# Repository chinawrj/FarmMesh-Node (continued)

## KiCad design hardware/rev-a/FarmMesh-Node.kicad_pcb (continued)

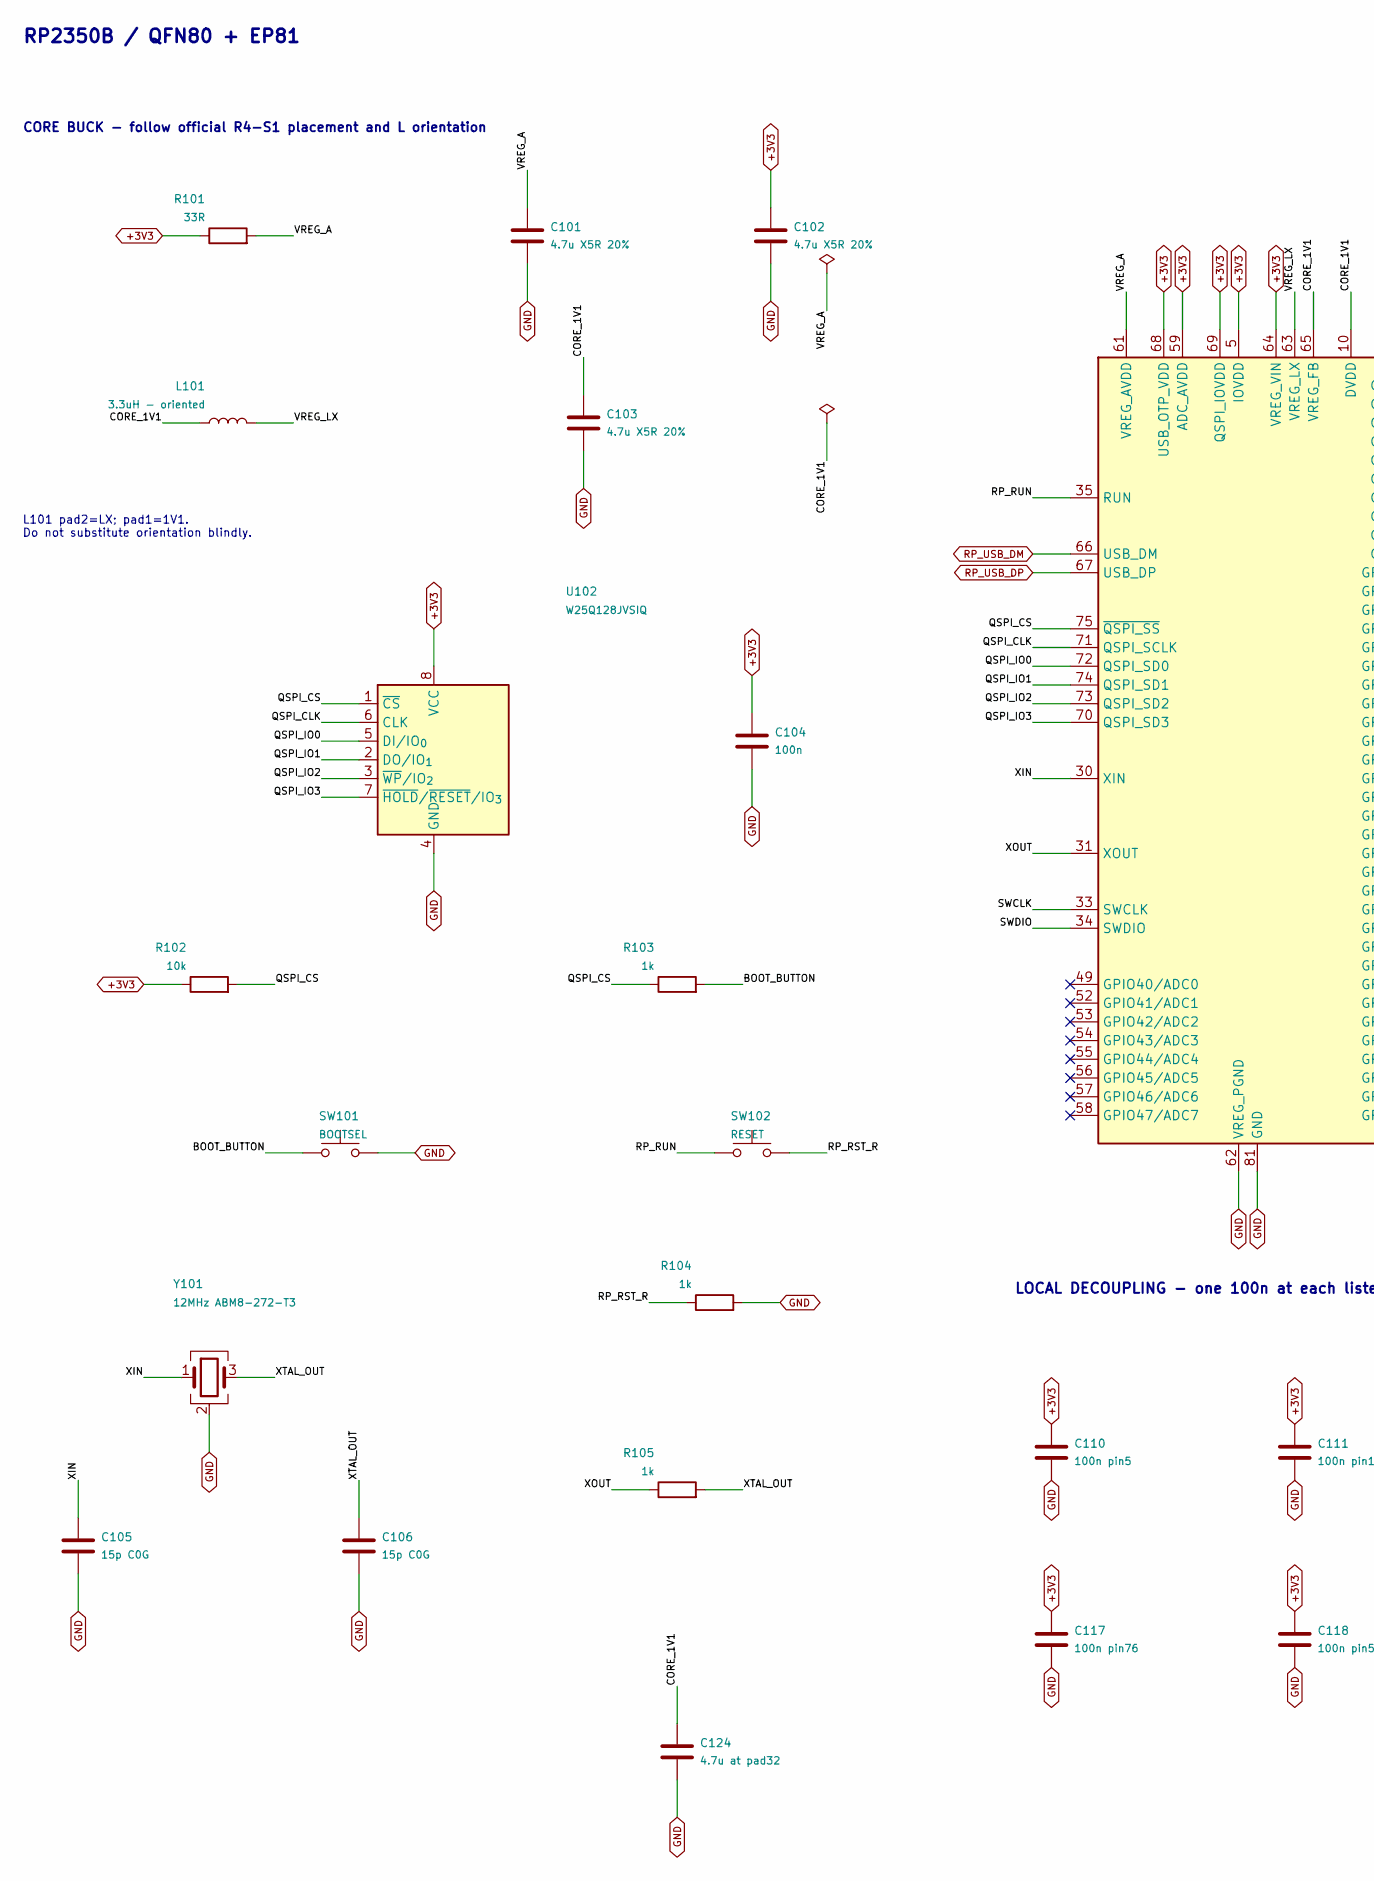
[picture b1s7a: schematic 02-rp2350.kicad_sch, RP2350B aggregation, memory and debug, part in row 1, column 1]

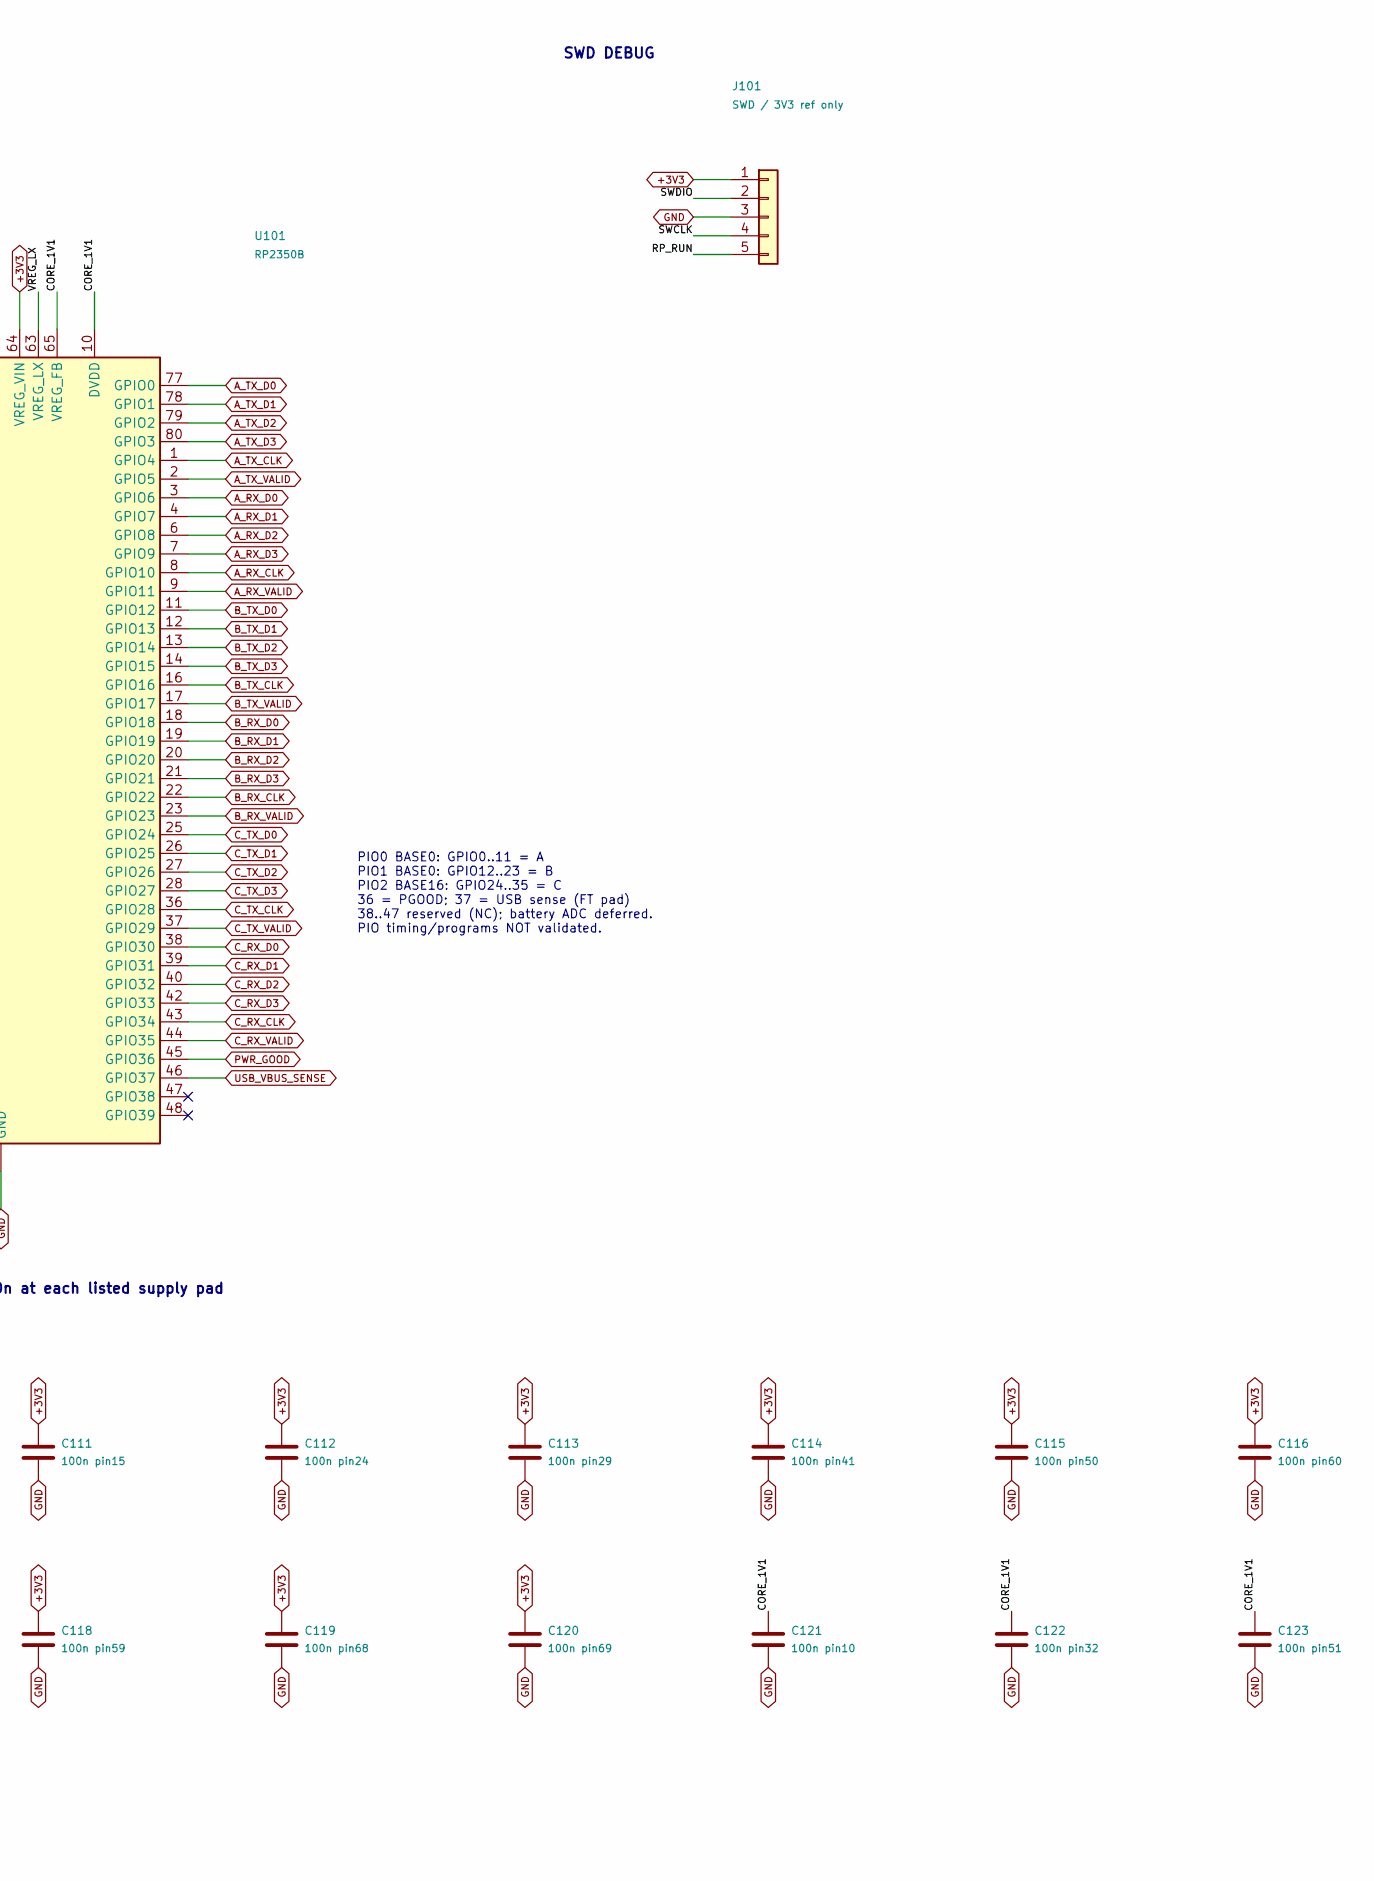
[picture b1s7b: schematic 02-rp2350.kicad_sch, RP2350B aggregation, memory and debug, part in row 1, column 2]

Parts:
C101, C102, C103: 4.7u X5R 20%; C_0603_1608Metric
C104: 100n; C_0603_1608Metric
C105, C106: 15p C0G; C_0603_1608Metric
C110: 100n pin5; C_0603_1608Metric
C111: 100n pin15; C_0603_1608Metric
C112: 100n pin24; C_0603_1608Metric
C113: 100n pin29; C_0603_1608Metric
C114: 100n pin41; C_0603_1608Metric
C115: 100n pin50; C_0603_1608Metric
C116: 100n pin60; C_0603_1608Metric
C117: 100n pin76; C_0603_1608Metric
C118: 100n pin59; C_0603_1608Metric
C119: 100n pin68; C_0603_1608Metric
C120: 100n pin69; C_0603_1608Metric
C121: 100n pin10; C_0603_1608Metric
C122: 100n pin32; C_0603_1608Metric
C123: 100n pin51; C_0603_1608Metric
C124: 4.7u at pad32; C_0603_1608Metric
J101: SWD / 3V3 ref only; PinHeader_1x05_P2.54mm_Vertical
L101: 3.3uH - oriented; AOTA-B201610S3R3-101-T; MPN AOTA-B201610S3R3-101-T
R101: 33R; R_0603_1608Metric
R102: 10k; R_0603_1608Metric
R103, R104, R105: 1k; R_0603_1608Metric
SW101: BOOTSEL; SW_Push_1P1T_NO_E-Switch_TL3301NxxxxxG
SW102: RESET; SW_Push_1P1T_NO_E-Switch_TL3301NxxxxxG
U101: RP2350B; QFN-80-1EP_10x10mm_P0.4mm_EP3.4x3.4mm; MPN RP2350B
U102: W25Q128JVSIQ; SOIC-8_5.3x5.3mm_P1.27mm; MPN W25Q128JVSIQ
Y101: 12MHz ABM8-272-T3; Crystal_SMD_3225-4Pin_3.2x2.5mm; MPN ABM8-272-T3

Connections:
+3V3: C102.1, C104.1, C110.1, C111.1, C112.1, C113.1, C114.1, C115.1, C116.1, C117.1, C118.1, C119.1, C120.1, J101.1, R101.1, R102.1, U101.5 (IOVDD), U101.15 (IOVDD), U101.24 (IOVDD), U101.29 (IOVDD), U101.41 (IOVDD), U101.50 (IOVDD), U101.59 (ADC_AVDD), U101.60 (IOVDD), U101.64 (VREG_VIN), U101.68 (USB_OTP_VDD), U101.69 (QSPI_IOVDD), U101.76 (IOVDD), U102.8 (VCC); also elsewhere on the board
/RP2350B aggregation, memory and debug/BOOT_BUTTON: R103.2, SW101.1
/RP2350B aggregation, memory and debug/QSPI_CLK: U101.71 (QSPI_SCLK), U102.6 (CLK)
/RP2350B aggregation, memory and debug/QSPI_CS: R102.2, R103.1, U101.75 (~QSPI_SS), U102.1 (~CS)
/RP2350B aggregation, memory and debug/QSPI_IO0: U101.72 (QSPI_SD0), U102.5 (DI/IO_{0})
/RP2350B aggregation, memory and debug/QSPI_IO1: U101.74 (QSPI_SD1), U102.2 (DO/IO_{1})
/RP2350B aggregation, memory and debug/QSPI_IO2: U101.73 (QSPI_SD2), U102.3 (~WP/IO_{2})
/RP2350B aggregation, memory and debug/QSPI_IO3: U101.70 (QSPI_SD3), U102.7 (~HOLD/~RESET/IO_{3})
/RP2350B aggregation, memory and debug/RP_RST_R: R104.1, SW102.2
/RP2350B aggregation, memory and debug/SWCLK: J101.4, U101.33 (SWCLK)
/RP2350B aggregation, memory and debug/SWDIO: J101.2, U101.34 (SWDIO)
/RP2350B aggregation, memory and debug/VREG_A: C101.1, R101.2, U101.61 (VREG_AVDD)
/RP2350B aggregation, memory and debug/VREG_LX: L101.2, U101.63 (VREG_LX)
/RP2350B aggregation, memory and debug/XIN: C105.1, U101.30 (XIN), Y101.1
/RP2350B aggregation, memory and debug/XOUT: R105.1, U101.31 (XOUT)
/RP2350B aggregation, memory and debug/XTAL_OUT: C106.1, R105.2, Y101.3
A_RX_CLK: U101.8 (GPIO10); also elsewhere on the board
A_RX_D0: U101.3 (GPIO6); also elsewhere on the board
A_RX_D1: U101.4 (GPIO7); also elsewhere on the board
A_RX_D2: U101.6 (GPIO8); also elsewhere on the board
A_RX_D3: U101.7 (GPIO9); also elsewhere on the board
A_RX_VALID: U101.9 (GPIO11); also elsewhere on the board
A_TX_CLK: U101.1 (GPIO4); also elsewhere on the board
A_TX_D0: U101.77 (GPIO0); also elsewhere on the board
A_TX_D1: U101.78 (GPIO1); also elsewhere on the board
A_TX_D2: U101.79 (GPIO2); also elsewhere on the board
A_TX_D3: U101.80 (GPIO3); also elsewhere on the board
A_TX_VALID: U101.2 (GPIO5); also elsewhere on the board
B_RX_CLK: U101.22 (GPIO22); also elsewhere on the board
B_RX_D0: U101.18 (GPIO18); also elsewhere on the board
B_RX_D1: U101.19 (GPIO19); also elsewhere on the board
B_RX_D2: U101.20 (GPIO20); also elsewhere on the board
B_RX_D3: U101.21 (GPIO21); also elsewhere on the board
B_RX_VALID: U101.23 (GPIO23); also elsewhere on the board
B_TX_CLK: U101.16 (GPIO16); also elsewhere on the board
B_TX_D0: U101.11 (GPIO12); also elsewhere on the board
B_TX_D1: U101.12 (GPIO13); also elsewhere on the board
B_TX_D2: U101.13 (GPIO14); also elsewhere on the board
B_TX_D3: U101.14 (GPIO15); also elsewhere on the board
B_TX_VALID: U101.17 (GPIO17); also elsewhere on the board
CORE_1V1: C103.1, C121.1, C122.1, C123.1, C124.1, L101.1, U101.10 (DVDD), U101.32 (DVDD), U101.51 (DVDD), U101.65 (VREG_FB); also elsewhere on the board
C_RX_CLK: U101.43 (GPIO34); also elsewhere on the board
C_RX_D0: U101.38 (GPIO30); also elsewhere on the board
C_RX_D1: U101.39 (GPIO31); also elsewhere on the board
C_RX_D2: U101.40 (GPIO32); also elsewhere on the board
C_RX_D3: U101.42 (GPIO33); also elsewhere on the board
C_RX_VALID: U101.44 (GPIO35); also elsewhere on the board
C_TX_CLK: U101.36 (GPIO28); also elsewhere on the board
C_TX_D0: U101.25 (GPIO24); also elsewhere on the board
C_TX_D1: U101.26 (GPIO25); also elsewhere on the board
C_TX_D2: U101.27 (GPIO26); also elsewhere on the board
C_TX_D3: U101.28 (GPIO27); also elsewhere on the board
C_TX_VALID: U101.37 (GPIO29); also elsewhere on the board
GND: C101.2, C102.2, C103.2, C104.2, C105.2, C106.2, C110.2, C111.2, C112.2, C113.2, C114.2, C115.2, C116.2, C117.2, C118.2, C119.2, C120.2, C121.2, C122.2, C123.2, C124.2, J101.3, R104.2, SW101.2, U101.62 (VREG_PGND), U101.81 (GND), U102.4 (GND), Y101.2 (G), Y101.4 (G); also elsewhere on the board
PWR_GOOD: U101.45 (GPIO36); also elsewhere on the board
RP_RUN: J101.5, SW102.1, U101.35 (RUN); also elsewhere on the board
RP_USB_DM: U101.66 (USB_DM); also elsewhere on the board
RP_USB_DP: U101.67 (USB_DP); also elsewhere on the board
USB_VBUS_SENSE: U101.46 (GPIO37); also elsewhere on the board

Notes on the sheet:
LOCAL DECOUPLING - one 100n at each listed supply pad
CORE BUCK - follow official R4-S1 placement and L orientation
PIO0 BASE0: GPIO0..11 = A PIO1 BASE0: GPIO12..23 = B PIO2 BASE16: GPIO24..35 = C 36 = PGOOD; 37 = USB sense (FT pad) 38..47 reserved (NC); battery ADC deferred. PIO timing/programs NOT validated.
RP2350B / QFN80 + EP81
L101 pad2=LX; pad1=1V1. Do not substitute orientation blindly.
SWD DEBUG

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
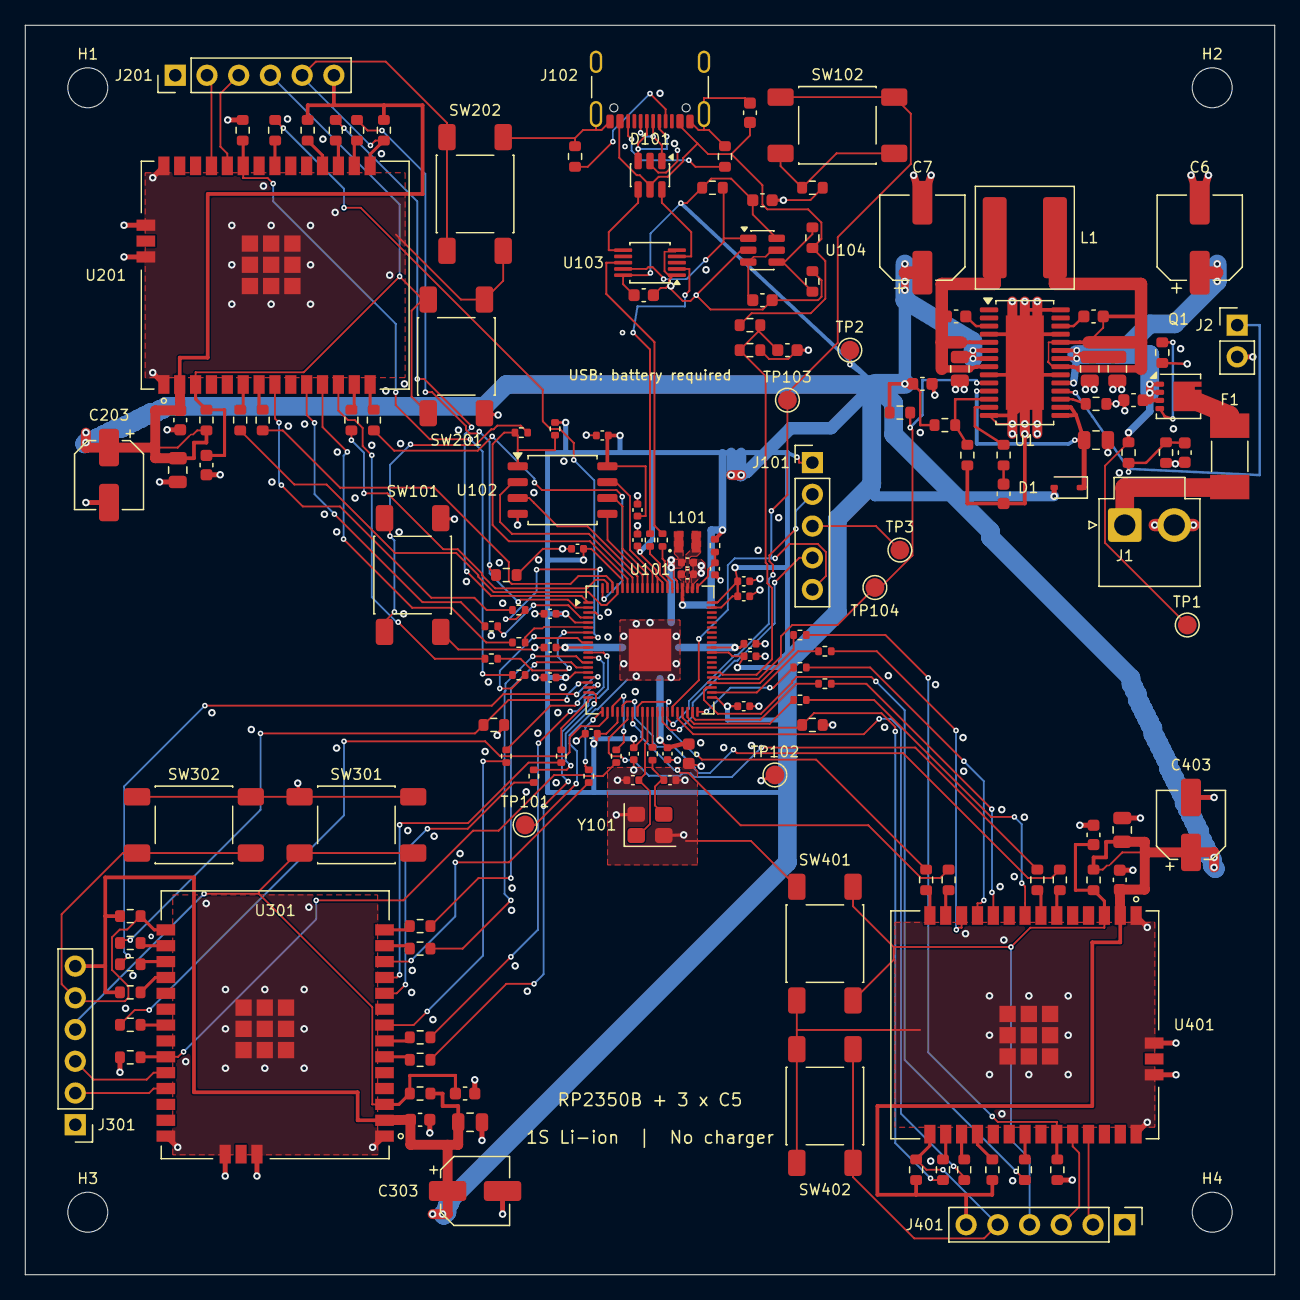
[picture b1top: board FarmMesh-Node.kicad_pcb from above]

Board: 4 copper layers, 100.0 x 100.0 mm, 164 parts (0 on the bottom side), 136 nets.

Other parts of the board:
C128: 100n / 16V at U103; C_0603_1608Metric
C129: 100n / 16V at U104; C_0603_1608Metric
C130: 1n C0G REF; C_0603_1608Metric
H1, H2, H3, H4: M3 / 3.2mm NPTH; MountingHole_3.2mm_M3
R114: 237k 0.1%; R_0603_1608Metric
R115: 100k 0.1%; R_0603_1608Metric
R116: 10k OE pull-up; R_0603_1608Metric
TP1: VBAT_PROTECTED; TestPoint_Pad_D1.5mm
TP2: +3V3; TestPoint_Pad_D1.5mm
TP3, TP102: GND; TestPoint_Pad_D1.5mm
TP101: CORE_1V1; TestPoint_Pad_D1.5mm
TP103: RP_RUN; TestPoint_Pad_D1.5mm
TP104: PWR_GOOD; TestPoint_Pad_D1.5mm
U103: TS3USB30EDGSR; TSSOP-10_3x3mm_P0.5mm
U104: TLV3011BIDBVR; SOT-23-6

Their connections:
+3V3: C128.1, C129.1, R116.1, TP2.1, U103.10, U104.6; also elsewhere on the board
/RP USB boot / self-powered USB-C/USB_DISCONNECT: R116.2, U103.9, U104.1
/RP USB boot / self-powered USB-C/USB_REF: C130.1, U104.3, U104.5
/RP USB boot / self-powered USB-C/USB_VBUS: R114.1; also elsewhere on the board
/RP USB boot / self-powered USB-C/USB_VBUS_CMP: R114.2, R115.1, U104.4
CORE_1V1: TP101.1; also elsewhere on the board
GND: C128.2, C129.2, C130.2, R115.2, TP3.1, TP102.1, U103.1, U103.5, U104.2; also elsewhere on the board
PWR_GOOD: TP104.1; also elsewhere on the board
RP_RUN: TP103.1; also elsewhere on the board
VBAT_PROTECTED: TP1.1; also elsewhere on the board

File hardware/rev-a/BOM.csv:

References,Quantity,Value,Manufacturer part number,Footprint,Selection status
"R1, R6",2,100k,,Resistor_SMD:R_0603_1608Metric,MPN TBD; footprint provisional
"R3, R8",2,100k 1%,,Resistor_SMD:R_0603_1608Metric,MPN TBD; footprint provisional
C104,1,100n,,Capacitor_SMD:C_0603_1608Metric,MPN TBD; footprint provisional
"C202, C302, C402, C5, C9",5,100n / 10V,,Capacitor_SMD:C_0603_1608Metric,MPN TBD; footprint provisional
"C1, C127, C2",3,100n / 16V,,Capacitor_SMD:C_0603_1608Metric,MPN TBD; footprint provisional
C121,1,100n pin10,,Capacitor_SMD:C_0603_1608Metric,MPN TBD; footprint provisional
C111,1,100n pin15,,Capacitor_SMD:C_0603_1608Metric,MPN TBD; footprint provisional
C112,1,100n pin24,,Capacitor_SMD:C_0603_1608Metric,MPN TBD; footprint provisional
C113,1,100n pin29,,Capacitor_SMD:C_0603_1608Metric,MPN TBD; footprint provisional
C122,1,100n pin32,,Capacitor_SMD:C_0603_1608Metric,MPN TBD; footprint provisional
C114,1,100n pin41,,Capacitor_SMD:C_0603_1608Metric,MPN TBD; footprint provisional
C110,1,100n pin5,,Capacitor_SMD:C_0603_1608Metric,MPN TBD; footprint provisional
C115,1,100n pin50,,Capacitor_SMD:C_0603_1608Metric,MPN TBD; footprint provisional
C123,1,100n pin51,,Capacitor_SMD:C_0603_1608Metric,MPN TBD; footprint provisional
C118,1,100n pin59,,Capacitor_SMD:C_0603_1608Metric,MPN TBD; footprint provisional
C116,1,100n pin60,,Capacitor_SMD:C_0603_1608Metric,MPN TBD; footprint provisional
C119,1,100n pin68,,Capacitor_SMD:C_0603_1608Metric,MPN TBD; footprint provisional
C120,1,100n pin69,,Capacitor_SMD:C_0603_1608Metric,MPN TBD; footprint provisional
C117,1,100n pin76,,Capacitor_SMD:C_0603_1608Metric,MPN TBD; footprint provisional
C6,1,100u / 10V bulk,,Capacitor_SMD:CP_Elec_6.3x5.8,MPN TBD; footprint provisional
"C203, C303, C403",3,100u / 6.3V bulk,,Capacitor_SMD:CP_Elec_6.3x5.8,MPN TBD; footprint provisional
"R102, R201, R202, R203, R301, R302, R303, R401, R402, R403",10,10k,,Resistor_SMD:R_0603_1608Metric,MPN TBD; footprint provisional
C126,1,10n,,Capacitor_SMD:C_0603_1608Metric,MPN TBD; footprint provisional
Y101,1,12MHz ABM8-272-T3,ABM8-272-T3,Crystal:Crystal_SMD_3225-4Pin_3.2x2.5mm,Draft selected; no stock check
"C105, C106",2,15p C0G,,Capacitor_SMD:C_0603_1608Metric,MPN TBD; footprint provisional
R5,1,162k 1%,,Resistor_SMD:R_0603_1608Metric,MPN TBD; footprint provisional
R7,1,174k 1%,,Resistor_SMD:R_0603_1608Metric,MPN TBD; footprint provisional
J1,1,1S Li-ion pack,B2P-VH(LF)(SN),Connector_JST:JST_VH_B2P-VH_1x02_P3.96mm_Vertical,Draft selected; no stock check
"R103, R104, R105",3,1k,,Resistor_SMD:R_0603_1608Metric,MPN TBD; footprint provisional
"C204, C304, C404",3,1u / 10V,,Capacitor_SMD:C_0603_1608Metric,MPN TBD; footprint provisional
C7,1,220u / 6.3V polymer,6SVPE220M,Capacitor_SMD:CP_Elec_6.3x5.9,Draft selected; no stock check
"R210, R211, R212, R213, R214, R215, R216, R217, R218, R219, R220, R221, R310, R311, R312, R313, R314, R315, R316, R317, R318, R319, R320, R321, R410, R411, R412, R413, R414, R415, R416, R417, R418, R419, R420, R421",36,22R,,Resistor_SMD:R_0603_1608Metric,MPN TBD; footprint provisional
"C201, C3, C301, C4, C401, C8",6,22u / 10V X7R,,Capacitor_SMD:C_0805_2012Metric,MPN TBD; footprint provisional
"R110, R111",2,27R at RP,,Resistor_SMD:R_0603_1608Metric,MPN TBD; footprint provisional
L101,1,3.3uH - oriented,AOTA-B201610S3R3-101-T,FarmMesh:AOTA-B201610S3R3-101-T,Draft selected; no stock check
R2,1,316k 1%,,Resistor_SMD:R_0603_1608Metric,MPN TBD; footprint provisional
R101,1,33R,,Resistor_SMD:R_0603_1608Metric,MPN TBD; footprint provisional
"R204, R205, R304, R305, R404, R405",6,4.7k VALID idle low,,Resistor_SMD:R_0603_1608Metric,MPN TBD; footprint provisional
C11,1,4.7u / 10V,,Capacitor_SMD:C_0805_2012Metric,MPN TBD; footprint provisional
"C101, C102, C103",3,4.7u X5R 20%,,Capacitor_SMD:C_0603_1608Metric,MPN TBD; footprint provisional
C124,1,4.7u at pad32,,Capacitor_SMD:C_0603_1608Metric,MPN TBD; footprint provisional
L1,1,4.7uH,XAL7070-472MEC,Inductor_SMD:L_Coilcraft_XAL7070-XXX,Draft selected; no stock check
C12,1,470p C0G,,Capacitor_SMD:C_0603_1608Metric,MPN TBD; footprint provisional
"R108, R109, R112",3,5.1k 1%,,Resistor_SMD:R_0603_1608Metric,MPN TBD; footprint provisional
F1,1,5A fuse,0451005.MRL,Fuse:Fuse_Littelfuse-NANO2-451_453,Draft selected; no stock check
R113,1,7.5k 1%,,Resistor_SMD:R_0603_1608Metric,MPN TBD; footprint provisional
R4,1,78.7k 1%,,Resistor_SMD:R_0603_1608Metric,MPN TBD; footprint provisional
C10,1,820p C0G,,Capacitor_SMD:C_0603_1608Metric,MPN TBD; footprint provisional
"SW202, SW302, SW402",3,BOOT,,Button_Switch_SMD:SW_Push_1P1T_NO_E-Switch_TL3301NxxxxxG,MPN TBD; footprint provisional
SW101,1,BOOTSEL,,Button_Switch_SMD:SW_Push_1P1T_NO_E-Switch_TL3301NxxxxxG,MPN TBD; footprint provisional
Q1,1,DMP2008UFG-7,DMP2008UFG-7,Package_SON:Diodes_PowerDI3333-8,Draft selected; no stock check
"U201, U301, U401",3,ESP32-C5-WROOM-1U-N8R8,ESP32-C5-WROOM-1U-N8R8,FarmMesh:ESP32-C5-WROOM-1U,Draft selected; no stock check
U1,1,LTC3119IFE#PBF,LTC3119IFE#PBF,Package_SO:TSSOP-28-1EP_4.4x9.7mm_P0.65mm_EP3.05x7.56mm,Draft selected; no stock check
J2,1,OFF jumper,,Connector_PinHeader_2.54mm:PinHeader_1x02_P2.54mm_Vertical,MPN TBD; footprint provisional
D1,1,PMEG2010EA,"PMEG2010EA,115",Diode_SMD:D_SOD-323,Draft selected; no stock check
"SW102, SW201, SW301, SW401",4,RESET,,Button_Switch_SMD:SW_Push_1P1T_NO_E-Switch_TL3301NxxxxxG,MPN TBD; footprint provisional
U101,1,RP2350B,RP2350B,Package_DFN_QFN:QFN-80-1EP_10x10mm_P0.4mm_EP3.4x3.4mm,Draft selected; no stock check
J101,1,SWD / 3V3 ref only,,Connector_PinHeader_2.54mm:PinHeader_1x05_P2.54mm_Vertical,MPN TBD; footprint provisional
"J201, J301, J401",3,UART / 3V3 reference only,,Connector_PinHeader_2.54mm:PinHeader_1x06_P2.54mm_Vertical,MPN TBD; footprint provisional
J102,1,USB4105-GF-A,USB4105-GF-A,Connector_USB:USB_C_Receptacle_GCT_USB4105-xx-A_16P_TopMnt_Horizontal,Draft selected; no stock check
D101,1,USBLC6-2SC6,USBLC6-2SC6,Package_TO_SOT_SMD:SOT-23-6,Draft selected; no stock check
U102,1,W25Q128JVSIQ,W25Q128JVSIQ,Package_SO:SOIC-8_5.3x5.3mm_P1.27mm,Draft selected; no stock check

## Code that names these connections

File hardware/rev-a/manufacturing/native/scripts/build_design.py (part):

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resistor(power,'R2','316k 1%',218.44,144.78,'+3V3','REG_FB')
resistor(power,'R3','100k 1%',279.4,144.78,'REG_FB','GND')
resistor(power,'R4','78.7k 1%',218.44,167.64,'REG_VC','COMP_RC')
capacitor(power,'C10','820p C0G',281.94,167.64,'COMP_RC',label_stub=0)
resistor(power,'R5','162k 1%',218.44,193.04,'REG_RT','GND')
capacitor(power,'C11','4.7u / 10V',281.94,198.12,'REG_VCC',footprint='Capacitor_SMD:C_0805_2012Metric',label_stub=0)
power.component('Device:D_Schottky','D1','PMEG2010EA',335.28,193.04,{'1':'REG_VCC','2':'+3V3'},footprint='Diode_SMD:D_SOD-323',mpn='PMEG2010EA,115')
resistor(power,'R6','100k',335.28,144.78,'+3V3','PWR_GOOD')
power.text('500kHz; VOUT = 0.795 x (1 + 316k/100k) = 3.307V nominal.\nMPPC tied to VCC (disabled). PWM/SYNC = GND (Burst allowed).\nSGND and PGND meet at exposed-pad ground; honor TA06 layout.\nD1: anode=3V3, cathode=VCC; do not short VCC to 3V3.',203.2,210.82,1.2)
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resistor(power,'R7','174k 1%',48.26,254,'VBAT_PROTECTED','REG_RUN')
resistor(power,'R8','100k 1%',116.84,254,'REG_RUN','GND')
capacitor(power,'C12','470p C0G',170.18,254,'REG_RUN')
power.component('Connector_Generic:Conn_01x02','J2','OFF jumper',226.06,254,{'1':'REG_RUN','2':'GND'},footprint='Connector_PinHeader_2.54mm:PinHeader_1x02_P2.54mm_Vertical')
power.text('RUN nominal: on 3.30V / off 3.01V; tolerances/load sag apply.\nNo external charger/PV input is provided.',259.08,243.84,1.2)
for i,net in enumerate(['GND','VBAT_PROTECTED']):power.component('power:PWR_FLAG',f'#FLG0{i+1}',net,35.56+i*30.48,205.74,{'1':net})

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for i,letter in enumerate('ABC'):
    for j,sig in enumerate(signals):rpn['GPIO'+str(i*12+j)]=letter+'_'+sig
rp.component('MCU_RaspberryPi:RP2350B','U101','RP2350B',190.5,119.38,rpn,mpn='RP2350B',fields=(224.79,50.8,224.79,53.34))
rp.text('PIO0 BASE0: GPIO0..11 = A\nPIO1 BASE0: GPIO12..23 = B\nPIO2 BASE16: GPIO24..35 = C\n36 = PGOOD; 37 = USB sense (FT pad)\n38..47 reserved (NC); battery ADC deferred.\nPIO timing/programs NOT validated.',238.76,134.62,1.2)
rp.text('CORE BUCK - follow official R4-S1 placement and L orientation',22.86,35.56,1.25,True)
resistor(rp,'R101','33R',50.8,50.8,'+3V3','VREG_A')
capacitor(rp,'C101','4.7u X5R 20%',91.44,50.8,'VREG_A')
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rp.component('Switch:SW_Push','SW101','BOOTSEL',66.04,175.26,{'1':'BOOT_BUTTON','2':'GND'},footprint='Button_Switch_SMD:SW_Push_1P1T_NO_E-Switch_TL3301NxxxxxG')
rp.component('Switch:SW_Push','SW102','RESET',121.92,175.26,{'1':'RP_RUN','2':'RP_RST_R'},footprint='Button_Switch_SMD:SW_Push_1P1T_NO_E-Switch_TL3301NxxxxxG')
resistor(rp,'R104','1k',116.84,195.58,'RP_RST_R','GND')
rp.component('Device:Crystal_GND24','Y101','12MHz ABM8-272-T3',48.26,205.74,{'1':'XIN','3':'XTAL_OUT','2':'GND','4':'GND'},footprint='Crystal:Crystal_SMD_3225-4Pin_3.2x2.5mm',mpn='ABM8-272-T3')
resistor(rp,'R105','1k',111.76,220.98,'XOUT','XTAL_OUT')
capacitor(rp,'C105','15p C0G',30.48,228.6,'XIN')
capacitor(rp,'C106','15p C0G',68.58,228.6,'XTAL_OUT')
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    capacitor(rp,'C'+str(110+i),'100n pin'+str(pad),x,y,net,label_stub=0)
capacitor(rp,'C124','4.7u at pad32',111.76,256.54,'CORE_1V1')
rp.text('SWD DEBUG',266.7,25.4,1.4,True)
rp.component('Connector_Generic:Conn_01x05','J101','SWD / 3V3 ref only',294.64,48.26,{'1':'+3V3','2':'SWDIO','3':'GND','4':'SWCLK','5':'RP_RUN'},footprint='Connector_PinHeader_2.54mm:PinHeader_1x05_P2.54mm_Vertical')

# A small dedicated USB sub-sheet keeps the dense RP decoupling page readable.
usb=Sheet('06-usb','RP USB boot / self-powered USB-C',7)
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capacitor(usb,'C129','100n / 16V at U104',337.82,213.36,'+3V3')
capacitor(usb,'C130','1n C0G REF',152.4,213.36,'USB_REF')

# Independent firmware VBUS sense remains on FT GPIO37; no ADC/battery sense.
resistor(usb,'R112','5.1k 1%',86.36,251.46,'USB_VBUS','USB_VBUS_SENSE')
resistor(usb,'R113','7.5k 1%',210.82,251.46,'USB_VBUS_SENSE','GND')
capacitor(usb,'C126','10n',269.24,248.92,'USB_VBUS_SENSE')
usb.component('power:PWR_FLAG','#FLG103','USB_VBUS',370.84,223.52,{'1':'USB_VBUS'})
usb.text('GPIO37: FT input; 5.1k/7.5k divider; disable internal pulls. U104 B variant required.\nU103 OE defaults high (disconnected). VBUS trip tolerances/power ordering need sample validation.\n90 ohm USB pair: J102 -> D101 -> U103 -> 27R near RP. Keep ESD on connector side.',25.4,271.78,1.15)

# Global cross-sheet nets also include RP USB and VBUS sensing.
# See GLOBAL_EXTRA in builder; this is an explicit interface, not a PCB route.
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for i,(s,letter) in enumerate(zip(radios,'ABC')):
    base=200+i*100
    s.text(f'ESP32-C5 MODULE {letter} / UART PROGRAMMING / INDEPENDENT 12-SIGNAL LINK',22.86,22.86,1.7,True)
    s.text('C5 TX and RX clocks both originate here. RP never drives either clock.\nUART0 download retained; C5 native USB disabled to release GPIO13/14.\nAll interface GPIOs avoid boot straps and internal Flash/PSRAM.',22.86,33.02,1.3)
    mn={'1':'GND','2':'+3V3','3':letter+'_EN','15':letter+'_BOOT','18':letter+'_STRAP27','24':letter+'_UART_RX','25':letter+'_UART_TX','28':'GND','29':'GND','30':'GND','32':'GND'}
    for pad,sig in zip(ordered,signals):mn[str(pad)]=letter+'_'+sig+'_C5'
    s.component(c5sym,f'U{base+1}','ESP32-C5-WROOM-1U-N8R8',101.6,116.84,mn,mpn='ESP32-C5-WROOM-1U-N8R8')
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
